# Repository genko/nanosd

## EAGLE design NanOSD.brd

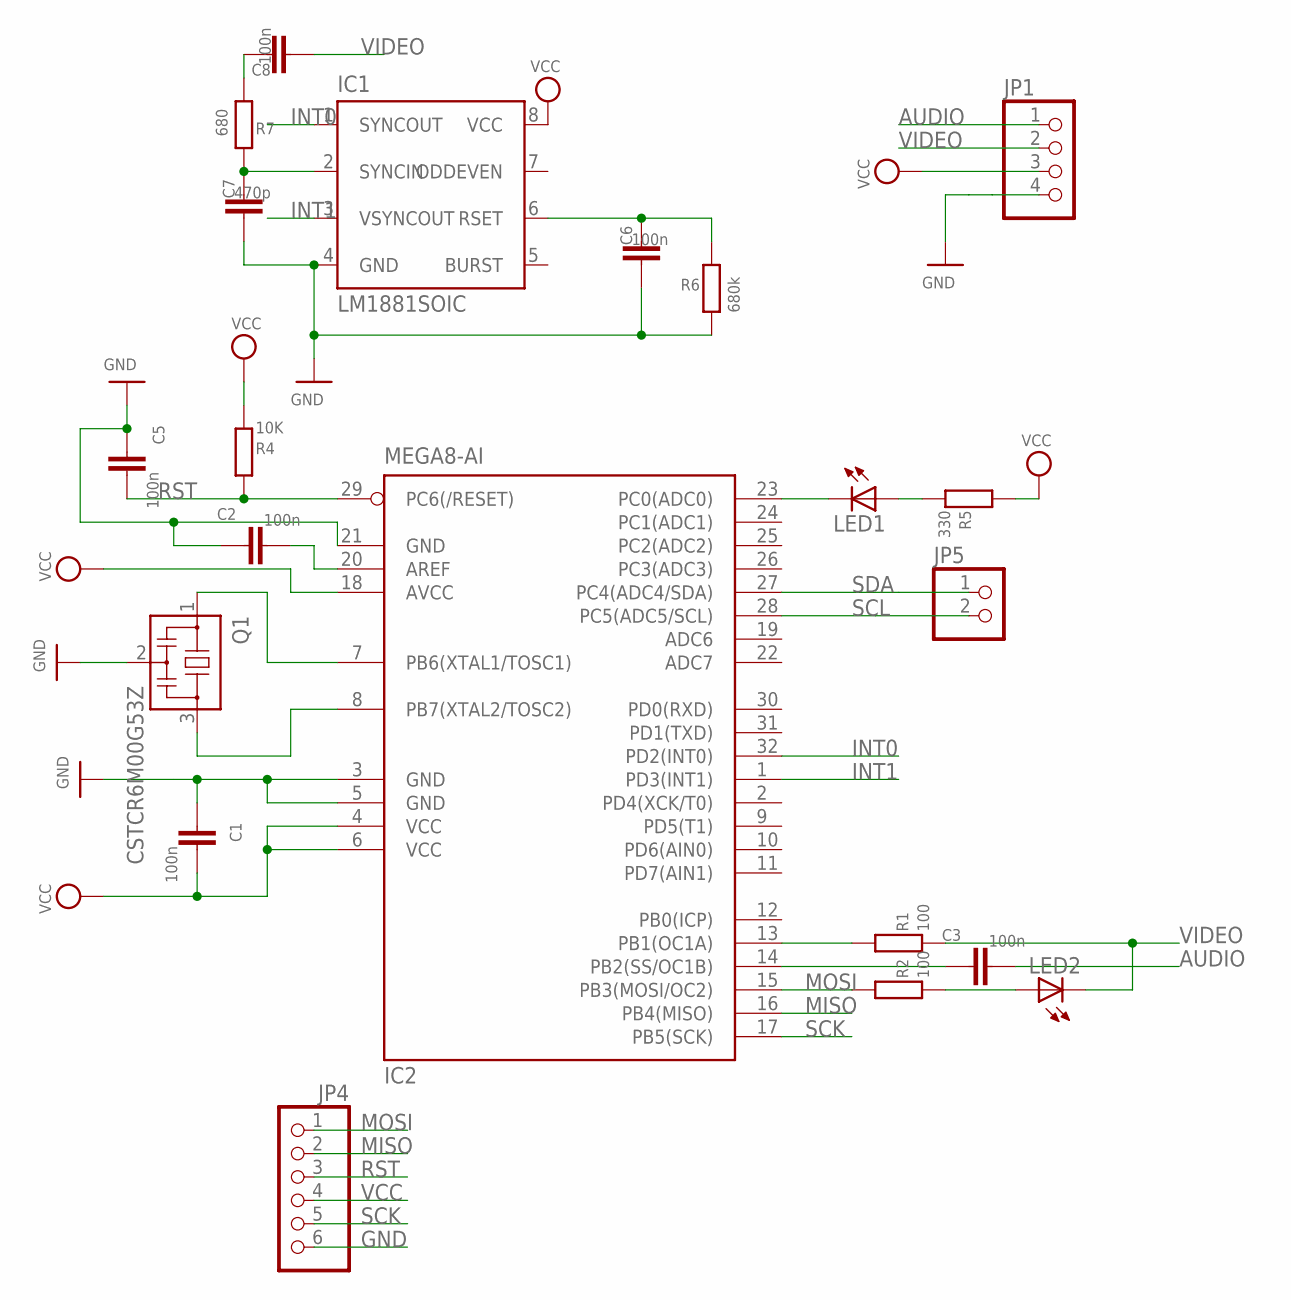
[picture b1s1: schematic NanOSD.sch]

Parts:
C1, C2, C3, C5, C6, C8: 100n; C0805
C7: 470p; C0805
IC1: LM1881SOIC; SO08
IC2: MEGA8-AI; TQFP32-08
JP1: PINHD-1X4; 1X04
JP4: PINHD-1X61.27MM; 1X06
JP5: PINHD-1X2; 1X02
LED1, LED2: LEDCHIP-LED0805; CHIP-LED0805
Q1: CSTCR6M00G53Z; CSTCR6M
R1, R2: 100; M0805
R4: 10K; M0805
R5: 330; M0805
R6: 680k; M0805
R7: 680; M0805

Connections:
AUDIO: C3.2, JP1.1
GND: C1.1, C2.1, C5.1, C6.1, C7.1, IC1.4 (GND), IC2.3 (GND), IC2.5 (GND), IC2.21 (GND), JP1.4, JP4.6, Q1.2, R6.2
INT0: IC1.1 (SYNCOUT), IC2.32 (PD2(INT0))
INT1: IC1.3 (VSYNCOUT), IC2.1 (PD3(INT1))
MISO: IC2.16 (PB4(MISO)), JP4.2
MOSI: IC2.15 (PB3(MOSI/OC2)), JP4.1, R2.2
unnamed: IC2.23 (PC0(ADC0)), LED1.C
unnamed: LED1.A, R5.1
unnamed: C6.2, IC1.6 (RSET), R6.1
unnamed: C7.2, IC1.2 (SYNCIN), R7.1
unnamed: IC2.13 (PB1(OC1A)), R1.2
unnamed: C8.2, R7.2
unnamed: IC2.7 (PB6(XTAL1/TOSC1)), Q1.1
unnamed: LED2.A, R2.1
unnamed: IC2.8 (PB7(XTAL2/TOSC2)), Q1.3
unnamed: C3.1, IC2.14 (PB2(SS/OC1B))
unnamed: C2.2, IC2.20 (AREF)
RST: C5.2, IC2.29 (PC6(/RESET)), JP4.3, R4.2
SCK: IC2.17 (PB5(SCK)), JP4.5
SCL: IC2.28 (PC5(ADC5/SCL)), JP5.2
SDA: IC2.27 (PC4(ADC4/SDA)), JP5.1
VCC: C1.2, IC1.8 (VCC), IC2.4 (VCC), IC2.6 (VCC), IC2.18 (AVCC), JP1.3, JP4.4, R4.1, R5.2
VIDEO: C8.1, JP1.2, LED2.C, R1.1

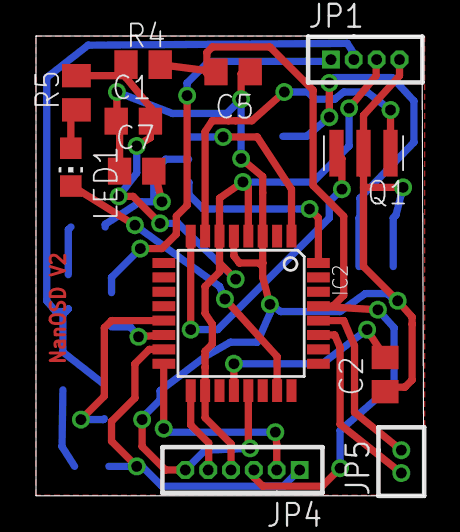
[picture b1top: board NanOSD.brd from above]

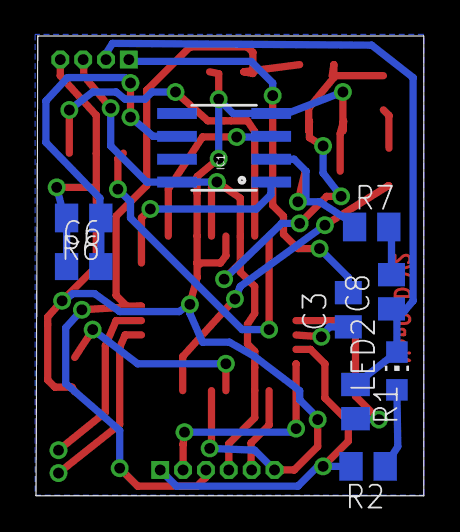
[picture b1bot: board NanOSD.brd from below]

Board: 2 copper layers, 21.5 x 25.5 mm, 21 parts (9 on the bottom side), 23 nets.

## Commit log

2013-06-21 Changed from attiny84 to atmega88
2013-06-26 Finished routing.
